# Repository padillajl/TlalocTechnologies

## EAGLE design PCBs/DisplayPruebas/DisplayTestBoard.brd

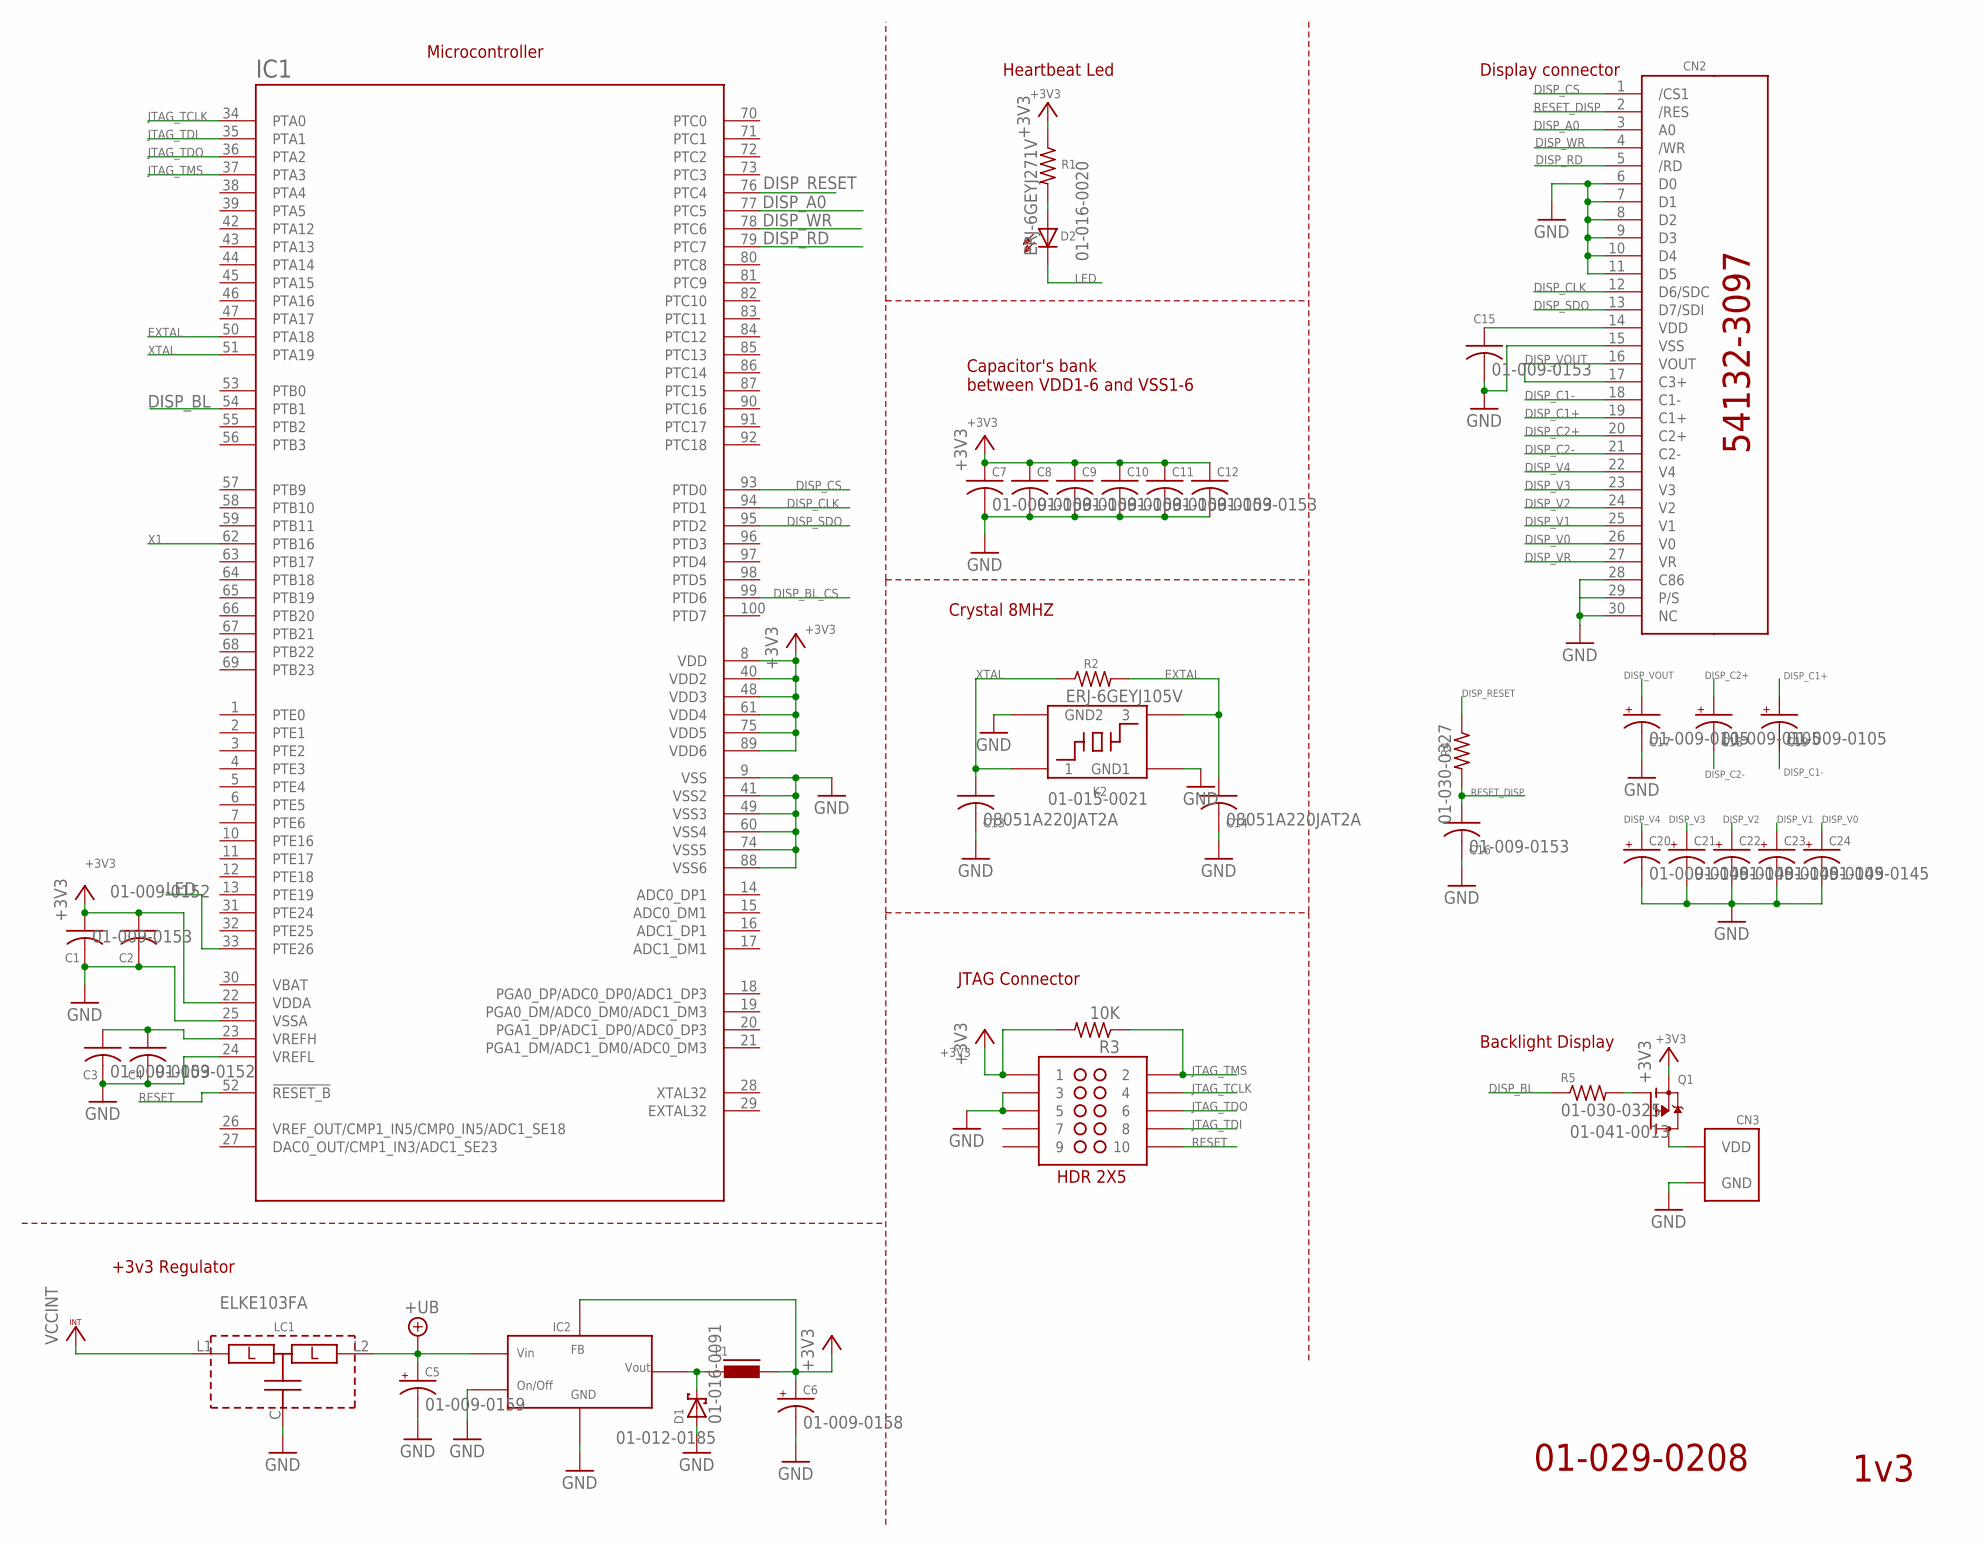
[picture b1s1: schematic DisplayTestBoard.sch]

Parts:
C1, C3, C7, C8, C9, C10, C11, C12, C15, C16: 01-009-0153; C0805
C2, C4: 01-009-0152; C0805
C5: 01-009-0159; PANASONIC_6.3MM
C6: 01-009-0158; PANASONIC_6.3MM
C13, C14: 08051A220JAT2A; C0805
C17, C18, C19: 01-009-0105; CT3528
C20, C21, C22, C23, C24: 01-009-0145; CT3528
CN2: 01-014-0371; XF2L-3035-1
CN3: 01-014-0372; S2B-PH-K-S
D1: 01-016-0091; SOD123
D2: 01-016-0020; LED0603
IC1: 01-012-0181; LQFP100
IC2: 01-012-0185; SO08
JTAG: SAMTECSTR2X5
K2: 01-015-0021; XTAL
L1: 01-023-0014; SRR1260
LC1: ELKE103FA
Q1: 01-041-0013; SOT-23
R1: ERJ-6GEYJ271V; M0805
R2: ERJ-6GEYJ105V; M0805
R3: 10K; M0805
R4: 01-030-0327; M0805
R5: 01-030-0325; M0805

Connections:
+3V3: C1.1, C2.1, C3.1, C4.1, C6.+, C7.1, C8.1, C9.1, C10.1, C11.1, C12.1, C15.1, CN2.14 (VDD), IC1.8 (VDD), IC1.22 (VDDA), IC1.23 (VREFH), IC1.40 (VDD2), IC1.48 (VDD3), IC1.61 (VDD4), IC1.75 (VDD5), IC1.89 (VDD6), IC2.4 (FB), JTAG.P$1 (1), L1.2, Q1.2 (S), R1.1, R3.2
DISP_A0: CN2.3 (A0), IC1.77 (PTC5)
DISP_BL: IC1.54 (PTB1), R5.1
DISP_BL_CS: IC1.99 (PTD6)
DISP_C1+: C19.+, CN2.19 (C1+)
DISP_C1-: C19.-, CN2.18 (C1-)
DISP_C2+: C18.+, CN2.20 (C2+)
DISP_C2-: C18.-, CN2.21 (C2-)
DISP_CLK: CN2.12 (D6/SDC), IC1.94 (PTD1)
DISP_CS: CN2.1 (/CS1), IC1.93 (PTD0)
DISP_RD: CN2.5 (/RD), IC1.79 (PTC7)
DISP_RESET: IC1.76 (PTC4), R4.1
DISP_SDO: CN2.13 (D7/SDI), IC1.95 (PTD2)
DISP_V0: C24.+, CN2.26 (V0)
DISP_V1: C23.+, CN2.25 (V1)
DISP_V2: C22.+, CN2.24 (V2)
DISP_V3: C21.+, CN2.23 (V3)
DISP_V4: C20.+, CN2.22 (V4)
DISP_VOUT: C17.+, CN2.16 (VOUT), CN2.17 (C3+)
DISP_VR: CN2.27 (VR)
DISP_WR: CN2.4 (/WR), IC1.78 (PTC6)
EXTAL: C14.1, IC1.50 (PTA18), K2.P$3 (3), R2.2
GND: C1.2, C2.2, C3.2, C4.2, C5.-, C6.-, C7.2, C8.2, C9.2, C10.2, C11.2, C12.2, C13.2, C14.2, C15.2, C16.2, C17.-, C20.-, C21.-, C22.-, C23.-, C24.-, CN2.6 (D0), CN2.7 (D1), CN2.8 (D2), CN2.9 (D3), CN2.10 (D4), CN2.11 (D5), CN2.15 (VSS), CN2.28 (C86), CN2.29 (P/S), CN2.30 (NC), CN3.GND, D1.A, IC1.9 (VSS), IC1.24 (VREFL), IC1.25 (VSSA), IC1.41 (VSS2), IC1.49 (VSS3), IC1.60 (VSS4), IC1.74 (VSS5), IC1.88 (VSS6), IC2.5 (ON/OFF), IC2.6 (GND), JTAG.P$2 (3), JTAG.P$3 (5), K2.P$2 (GND1), K2.P$4 (GND2), LC1.C
JTAG_TCLK: IC1.34 (PTA0), JTAG.P$7 (4)
JTAG_TDI: IC1.35 (PTA1), JTAG.P$9 (8)
JTAG_TDO: IC1.36 (PTA2), JTAG.P$8 (6)
JTAG_TMS: IC1.37 (PTA3), JTAG.P$6 (2), R3.1
LED: D2.K (C), IC1.33 (PTE26)
unnamed: D1.C, IC2.8 (VOUT), L1.1
unnamed: CN3.VDD, Q1.3 (D)
unnamed: Q1.1 (G), R5.2
unnamed: D2.A, R1.2
RESET: IC1.52 (!RESET_B), JTAG.P$10 (10)
RESET_DISP: C16.1, CN2.2 (/RES), R4.2
VCCINT: LC1.L1
VMAIN: C5.+, IC2.7 (VIN), LC1.L2
X1: IC1.62 (PTB16)
XTAL: C13.1, IC1.51 (PTA19), K2.P$1 (1), R2.1

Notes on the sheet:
Crystal 8MHZ
Capacitor's bank between VDD1-6 and VSS1-6
Display connector
+3v3 Regulator
01-029-0208
1v3
Backlight Display
Heartbeat Led
Microcontroller
JTAG Connector

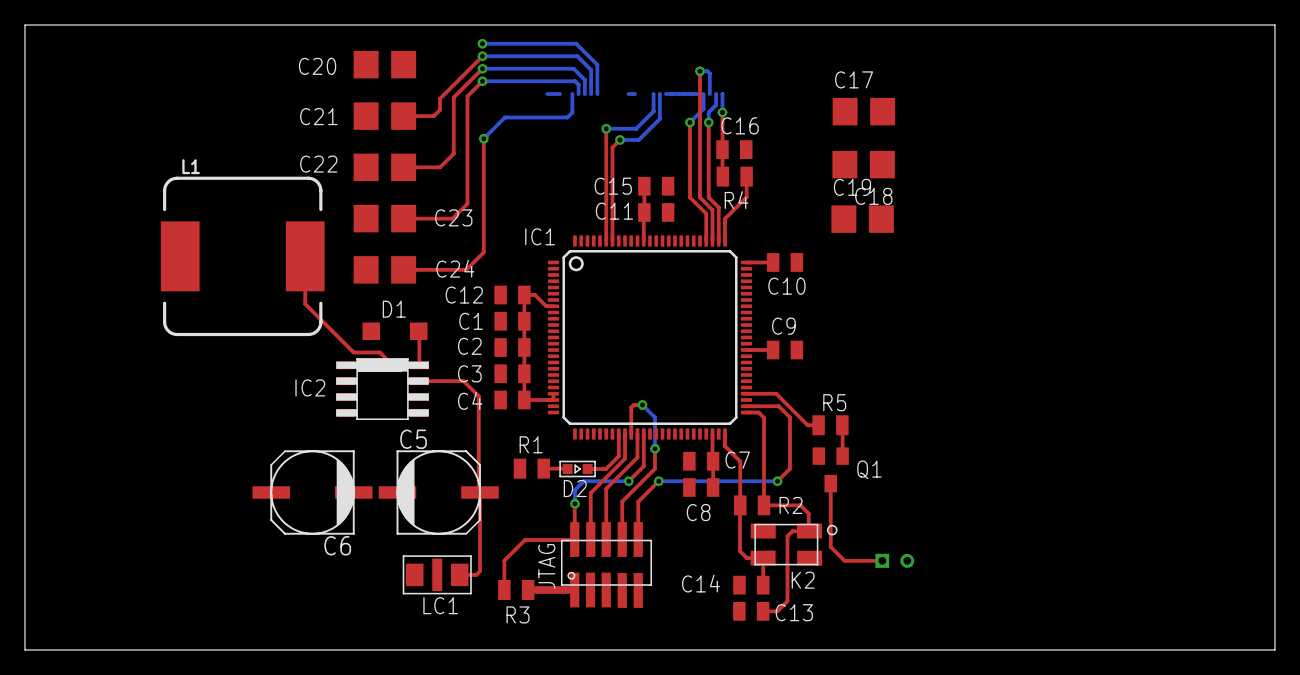
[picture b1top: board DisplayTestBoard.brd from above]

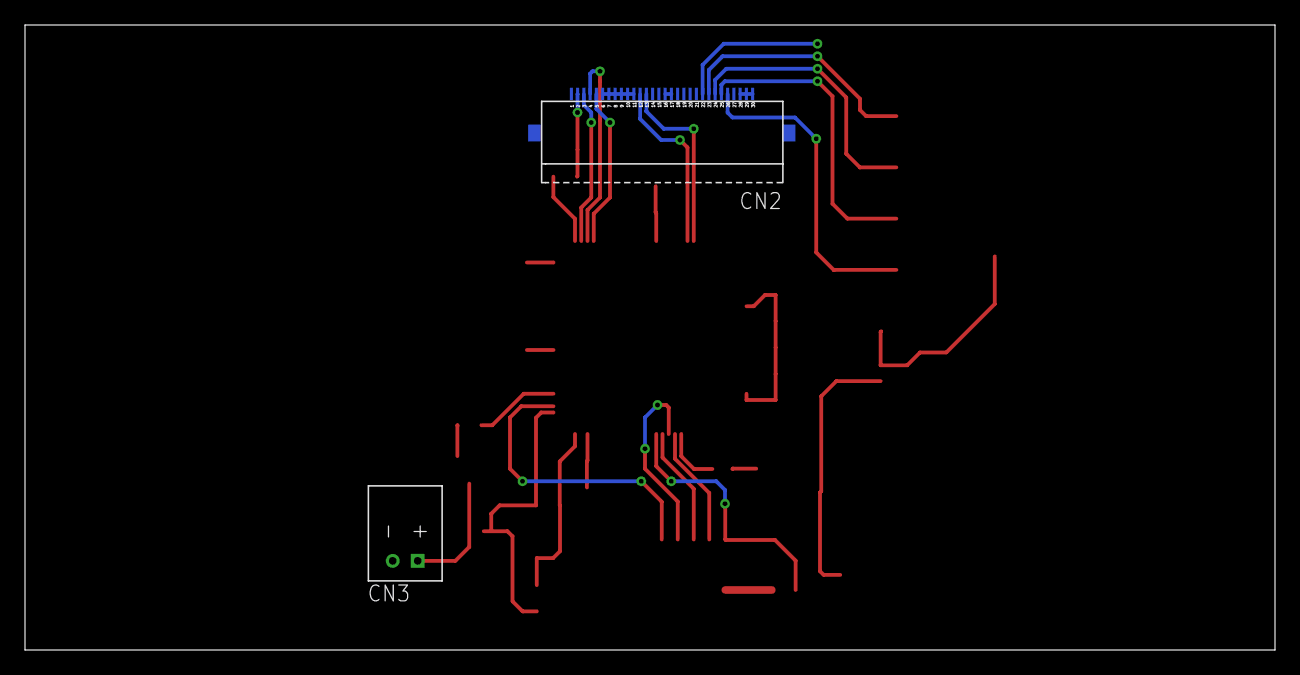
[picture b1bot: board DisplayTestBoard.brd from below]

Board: 2 copper layers, 100.0 x 50.0 mm, 40 parts (2 on the bottom side), 34 nets.

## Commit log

2018-07-18 Archivos de C Embebido
    Se suben archivos de C embebidos del proyecto
2018-07-18 LCD changes
    Se diseña driver para controlar LCD
2018-07-19 Comit 1
    Comit1
2018-07-20 Commit2
    Comit
2018-07-23 Actualizacion:MiscFunctions
    Se añaden rutinas para convertir de binario a BCD y se elimina rutina de LCD que convertia el valor a ASCII
2018-07-24 Version<OX02>
    <MEJORA>
    -Se fusiona el driver de sensores infrarrojos, con el de control de sensores.
    -Se añade un arreglo de los timers existentes y una enumeración para cada Timer en el Driver de SwTimers
2018-07-25 Version<OX03>
    Se une el modulo de sensores infrarrojos con el modulo de SensorsDriver
2018-07-26 Version <OX04>
    Se realizan pruebas de la versión OX03, ajustando detalles se logra mostrar la pantalla principal, y el mensaje de valvula encendida y valvula apagada, falta mostrar el mensaje de bienvenida, de tlal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
2018-07-30 Version <OX5>
    Se corrige bug de mensaje principal y se elimina la funcionalidad de un sensor infrarrojo y se convierte en uno solo el boton de ON/OFF
2018-08-17 Version OX06
    Se corrige valvula encendido y apagado, y se corrigen banderas de los timers del adc y sensor de flujo
2018-08-18 version OX07
    Se corrige el mostrar los litros en pantalla junto con el letrero de LTS: y TEMP:
    Se deja el valor de los litros a mostrar ya sin zeros.
2019-02-13 Test_TranceptorRF_OX01
    Se añade versión de pruebas de tranceptor RF
2019-02-13 1v1
    Initial Versión
2019-02-19 1v1
    Se modifican Componentes de Processor Expert
2019-03-22 Versión OX 02
    Se añade soporte para configuración de módulos de RF
2019-03-29 Version antes de fin de semana
    123
2019-05-10 asdasd
    sdasd
2019-05-17 OX01
2019-06-04 Wifi Info
    Se agrega información Wifi
2019-06-06 Back Up 06/06/19
    Back Up 06/06/19
2019-06-07 Back Up
2019-06-21 BackUP 21/06/19
2019-09-11 No idea
    No idea
2019-09-20 <OX UPDATE 01> <ADD>
    Se hace el desarrollo de Firmware para lograr la primera comunicación con módulo WiFi enviando un comando AT sencillo
2019-09-24 <OX UPDATE 02> <ADD>
    Se abre proyecto para hacer pruebas de RTC
2019-09-27 <OX UPDATE 03> <ADD>
    Se culminan pruebas satisfactorias del RTC del KL25z
2019-10-01 Se agrega Esquemático y Board de PCB de pruebas de Display
2019-10-01 Se agregan documentos para la continuidad de desarrollo de Display
2019-10-07 Repository Clean Up
    Se hace limpieza de repositorio
2019-10-11 <OX UPDATE 04>
    Se hacen pruebas de conectividad al WiFi del celular
